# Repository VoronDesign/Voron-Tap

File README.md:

# Voron Tap

> Animated image courtesy of [Maple Leaf Makers](https://github.com/MapleLeafMakers) , see the whole video at https://www.youtube.com/watch?v=mz5qcOZgXhI

Tap is a nozzle-based z-probe for the V2 and Trident printer designs. The entire toolhead moves to trigger an optical switch. Tap offers many advantages:

* Extreme precision 0.4μm (0.0004mm)
* Any build surface and easily change at will
* Durability via optical sensor (millions of probe cycles)
* High temperature reliability (70C to 100C)
* Simplified probe mechanics (no dock/undock macros)
* No separate Z-endstop required
* Crash protection

## Requirements

* Bed must be stable for probing force of 500-800 grams
  * Switchwire, V1.8, Legacy, V0 beds are NOT rigid enough
* Mounts to MGN-12H X-axis
* Front mounted extruder (Clockwork2, LGX, Galileo)
* Accuracy depends on good mechanical condition
* Must have 5V at toolhead or special 24V sensor PCB

## Instructions

Comprehensive assembly details are available in the [Manual](Manual/Assembly_Manual_Tap.pdf)

## Post-Install Setup

1. Update your `printer.cfg` as recommended in [Tap Klipper Instructions](config/tap_klipper_instructions.md)
2. Test virtual Z endstop by lifting tool-head and using the `M119` or `query_probe` commands
3. Home Z.
4. Heat soak your machine and run a couple `probe_accuracy samples=100` to "break-in" your probe and check there's no significant trend in the result
5. Run a few more `probe_accuracy` checks (default of 10 probes)

### Diagnosing problems

For well-built machines you can expect to see between 0.0000 and 0.0008 standard deviation. Where probe accuracy trends notably up/down over 100 samples, or standard deviation is outside the desired range, check that:
- Sampling is taking place at a constant temperature (cooling/heating of any part will result in drift)
- Z belts are tightened correctly and uniformly
- The magnets on your tap have been adjusted to mate correctly when Tap is in the down position ([see the adjustment step in Nero3D's build guide](https://youtu.be/mJNCn72lQpU?t=751))
- The rail is well greased, the balls are correctly seated and there's no swarf in the guides (eg from the manufacture)
- The StealthBurner is firmly attached onto the Tap carriage
  - A common mistake is that the tabs on the body of the SB are pushed up under the alignment screws on the carriage to seat it in place, but then not tightened - make sure to tighten these firmly!
- The `speed` parameter in the `[probe]` section of your `printer.cfg` is appropriate (try `speed: 3` with `lift_speed: 10`)
- Several runs of `probe_accuracy samples=100` have been run (it can take a little while to bed in the rail)

While originally intended for the klicky probe, the following [probe accuracy tests](https://github.com/sporkus/probe_accuracy_tests) may assist in further diagnosis.

## FAQs

* Will Tap hurt my print surface? No, probing temp is restricted to 150C. The team recommends spray coated spring steel. Users of smooth PEI may find minor burnish marks if continously probing the same spot.
* Will the hartk 2-piece PCB work with Tap? Yes, but it requires a slight modification. See discord pin.
* Can I use an optical sensor not specified in the BOM? Not recommended, the team spent considerable time validating sensors in [BOM](BOM.md).
* Can I use micro-switch instead? Not recommended, but check here for more details: [Unklicky Tap](https://github.com/majarspeed/Unklicky/tree/main/Unklicky_TAP)
* Can I use Tap with kinematic bed mounts? Yes, if your bed is rigid up to 800 grams of force.
* Doesn't this add a lot of weight? The team explored many designs and landed on ~50 extra grams as good trade-off between rigidity and weight.
* Why do I need this if my induction probe works fine? Tap enables a far better user experience as it eliminates most baby-stepping needed due to thermal expansion, nozzle & bed surface changes.
* Is Tap noticably more accurate than klicky? Yes.

## (Bonus Points) Data Science

Tap engineering is backed by data science. If you want to dive deeper check out the following resources:

* [Voron:LIVE! Voron Tap announcement stream](https://www.youtube.com/watch?v=JLUDLJQXZeU)
* [Probe accuracy across thermal envelope](https://github.com/KiloQubit/probe_accuracy)
* [Repeatability at individual corners](https://github.com/sporkus/probe_accuracy_tests)

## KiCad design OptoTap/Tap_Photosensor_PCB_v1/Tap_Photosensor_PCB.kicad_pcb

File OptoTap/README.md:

# OptoTap PCB

OptoTap PCB is a small, completely unnecessary PCB that exists to make installation of the optical sensor marginally more convenient. (That's right, several of us have spent dozens of hours and hundreds of dollars in order to avoid two solder joints and a bit of heat shrink.)

It comes in two official flavors/form factors:

- **V1**: smaller form factor, 5V only
- **V2**: taller form factor, 5 or 24V capable

Both simplify optical sensor installation by including the necessary current-limiting resistor for the IR led within the sensor itself, as well as providing a visible LED indicator to assist with troubleshooting. 

The V1 board attempts to minimize size and cost as much as possible, at the expense of some flexibility: it **can not be used as a drop-in replacement for 24V inductive sensors** (24V will fry the optical sensor, eventually.)

The V2 board adds a switch-mode regulator to allow safely connecting to 24V probe headers. The regulator converts positive input voltage between >5V and 24V to 5V on-board, at the expense of some additional components and a larger PCB. **Please read important information about previous versions of this board below.**

## OptoTap V1

This version saves some vertical room by requiring you to solder your connector wires directly to the board.

**Do not connect this version to 24V!** (Did we mention that *it's not 24V tolerant???*) Many of the Voron toolhead PCBs in circulation send 24V to the three-pin probe header. You cannot plug this board directly in to these headers!

### Revision history 

- 1.0: initial release
- 1.3: updated release
	- hybrid footprint to permit use of EE-SX398 sensor in addition to Optek versions
	- two-color LED to indicate status and assist with troubleshooting.
	- 'Dark Mode' solder jumper to allow turning off indicator LEDs
	- increased thermal relief on solder pads to make through-holes easier to solder

## OptoTap V2

This version uses an AP63205WU switch mode regulator to drop input voltage and supply 5V to the sensor. This gives a bit of additional room to add a 3-pin JST-PH 2.0mm pitch connector as well [part number S3B-PH-K-S (LF)(SN)].

**IMPORTANT NOTE: The original version of this board had an issue that rendered it unsafe for use at 24V**. Please see [this issue](https://github.com/VoronDesign/Voron-Tap/issues/42#issuecomment-1370065351) for more extensive details on the testing and resolution of the problem. 

The current version (V2.4) fixes the inrush overvoltage spike that plagued the initial release, and adds several additional safeguards, including a polyfuse and a reverse polarity protection diode.

### Usage notes

#### Operation at 5V

The V2.4 OptoTap PCB has been tested to work fine from 5V to 24V inputs with no modifications. However, this does induce a bit of additional voltage drop from the switching regulator IC going into LDO mode. If you would like to run the V2.4 OptoTap at 5V, my first suggestion would be to just run it at 5V with no modifications. It will most likely work just fine. 

However, it does have the capacity to bypass the whole buck converter circuit. Note that this also bypasses the polyfuse, so there will be no overcurrent protection. 

To make this modification, you need to cut the trace between the center pad and 24V pad on the rear of the PCB, then use some solder to bridge the center pad to the 5V pad. To reverse the change, just desolder that bridge and re-connect the center pad to the 24V pad with more solder. 

### Revision history

- 2.0: initial prototype
- 2.1: component modifications after initial testing
  - changed C1 to higher voltage rating
  - changed C2 bootstrap cap to higher capacitance
  - changed all capacitors to 0805 for better part availability
- 2.4: updated release
  - added polyfuse to limit overcurrent and damp inrush current-induced voltage spike on hot-plugging
  - added reverse polarity protection diode 
  - increased size of inductor to prevent coil saturation
  - added a second output filter capacitor to reduce output voltage ripple
  - hybrid footprint to permit use of EE-SX398 sensor in addition to Optek versions
  - two-color LED to indicate status and assist with troubleshooting.
  - 'Dark Mode' solder jumper to allow turning off indicator LEDs
  - added 5V/24V selection solder jumper on rear of board to allow for easy bypassing of voltage regulator circuit
  - increased thermal relief on solder pads to make through-holes easier to solder

### Ordering and Assembly notes

#### Inductor choice

I've tested version of this PCB with inductors from Cenker 
CKCS3012-4.7uH/M (C354557) and Microgate 
MPIT3015-4R7M-LF (C486485). Any 30xx footprint coil inductor with >1A current rating and ~ 100 mΩ DCR should work ok.

#### Indicator LED placement

For some reason, JLCPCB has trouble with their part orientation for this LED specifically. I'm hoping that eventually they will sort their database out. In the meantime, it is worth verifying the part placement prior to assembly.

The footprint silkscreen has two elements to help indicate the orientation of the LED: an extra line on the side to indicate Pin 1, and a little arrow that matches up with a corresponding arrow on the part:

For the v2.4 PCB, make sure that the arrow on the DFM points to the arrow on the footprint, pin 1 matches the extra line on the footprint, and the + pad matches up to the correct pad! 

This is how it will look when assembled:

You can see the little bond wires from each of the three LEDs going back to the common anode, which is pretty neat.

***NOTE THAT THE 5V ONLY BOARD (V1.3) HAS A ROTATED FOOTPRINT! YOU'RE WELCOME AND I'M SORRY.***

## Indicator LEDs

The revised boards (V1.3/2.4) now have two-color indicator LEDs to help assist with troubleshooting. This should hopefully help a little bit with troubleshooting. The expected behavior of the LED is:

- Blue: Connected to power, beam not broken
- Red: Connected to power, beam broken

When installed in the toolhead, the light should be red normally (toolhead in 'down' position) and blue when activated (toolhead in 'up') position.

I would suggest powering on the board with 5V prior to installing it to make sure everything is functioning as expected. If the indicator LED is red with nothing blocking the optical sensor beam path, there is probably a problem with the ground and signal wires -- triple check!

## Sensor Choice

### Omron or Optek

The revised versions of the boards (V1.3 and V2.4) feature a hybrid optical sensor footprint that permits installation of the Omron EE-SX398 sensor in addition to the Optek OPB666/9xx versions. In testing, the Omron sensor performed just as well as the Optek sensor. 

However, it has a *slightly* different footprint than the Omron sensor, with annoyingly-close leads on the three pin side. I went through a few iterations of testing to come up with a hybrid footprint that seems to work well for either sensor model.

The slots mean there is a little play in sensor positioning, particularly with the EE-SX398 sensor. To help ensure precise alignment with this sensor, print out the jig included in the [STLs](./STLs) folder.

### Sensor Logic

The Tap setup requires a *buffer* style circuit rather than an *inverter* style to ensure safe operation. This style causes the sensor to trigger (pull the signal pin low) when the toolhead is in its normal, 'down' position. That means that if there is a bad connection somewhere, the MCU can observe that there is a problem *without* crashing the toolhead uncontrollably into the build plate.

Please double check your sensor part number to make sure you're getting the appropriate model!

#### For Omron:

- **Good**:
  - EE-SX398
- **Bad**: 
  - EE-SX498

#### For Optek:

- **Good**: 
  - OPB666N
  - OPB9x1
- **Bad**:
  - OPB9x2

Additionally, for the Optek probes, the OPB9x0 sensors are totem pole rather than open collector, meaning that they will pull the sense pin up to 5V when not pulling it down to GND. This can cause problems for some boards (notably RP2040-based CAN toolhead boards) that do not have 5V-tolerant endstop pins.

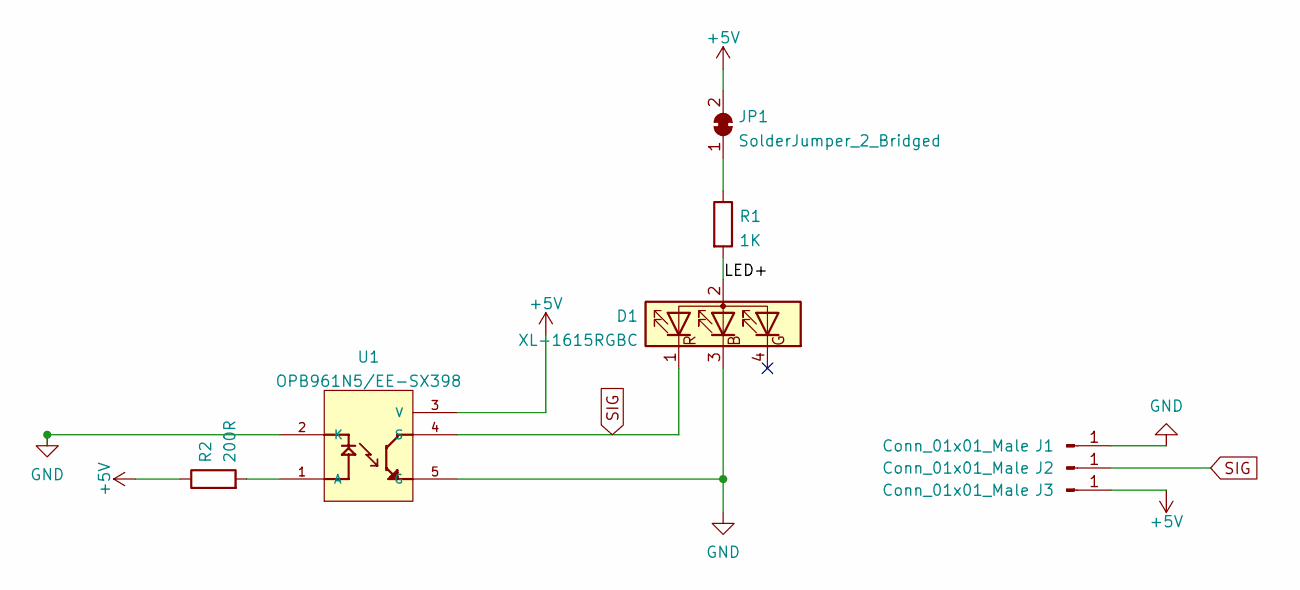
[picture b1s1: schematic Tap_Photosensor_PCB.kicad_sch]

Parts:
D1: XL-1615RGBC; LED_0606_1432; LCSC C965840
J1, J2, J3: Conn_01x01_Male; PinHeader_1x01_P2.54mm_Vertical
JP1: SolderJumper_2_Bridged; SolderJumper-2_P1.3mm_Bridged_RoundedPad1.0x1.5mm
R1: 1K; R_0805_2012Metric; LCSC C17513
R2: 200R; R_0805_2012Metric; LCSC C17540
U1: OPB961N5/EE-SX398; OPTO_EE-SX398_OPB666N; PARTREV NA

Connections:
+5V: J3.1, JP1.2 (B), R2.1, U1.3 (V)
/LED+: D1.2 (A), R1.2
GND: D1.3 (B), J1.1, U1.2 (K), U1.5 (G)
unnamed: JP1.1 (A), R1.1
unnamed: R2.2, U1.1 (A)
SIG: D1.1 (R), J2.1, U1.4 (S)

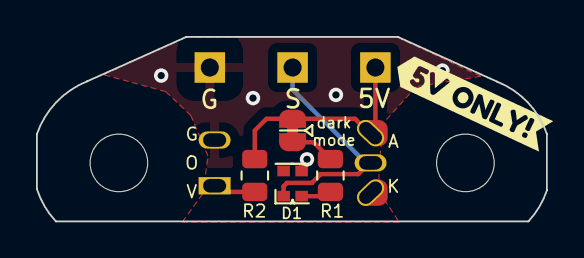
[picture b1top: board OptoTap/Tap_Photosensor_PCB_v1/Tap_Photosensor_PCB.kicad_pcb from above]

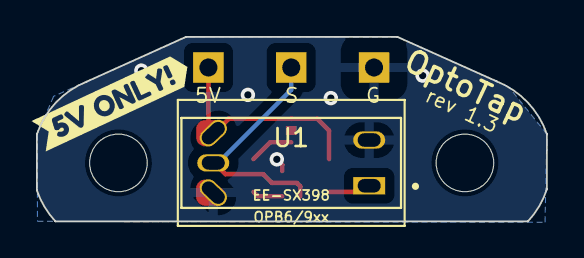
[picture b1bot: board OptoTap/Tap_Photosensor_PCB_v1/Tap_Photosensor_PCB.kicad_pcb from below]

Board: 2 copper layers, 28.3 x 10.2 mm, 10 parts (2 on the bottom side), 6 nets.

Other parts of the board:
kibuzzard-6366BF75: G***; kibuzzard-6366BF75
kibuzzard-6366C103: G***; kibuzzard-6366C103

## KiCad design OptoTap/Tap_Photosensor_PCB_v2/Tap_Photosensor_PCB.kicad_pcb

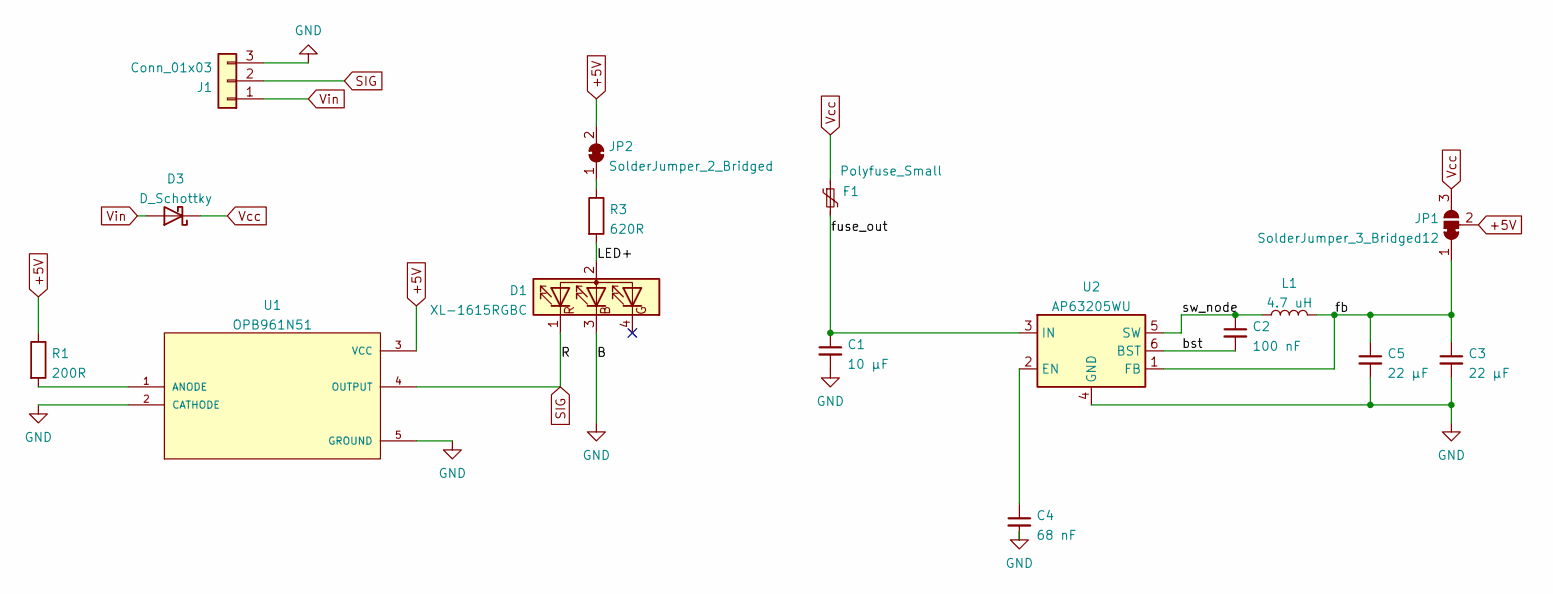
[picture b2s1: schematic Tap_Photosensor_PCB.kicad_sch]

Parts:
C1: 10 µF; C_0805_2012Metric; PARTNUM GRM21BR61H106KE43L; LCSC C440198
C2: 100 nF; C_0402_1005Metric; PARTNUM CL05B104KB54PNC; LCSC C307331
C3, C5: 22 µF; C_0603_1608Metric; PARTNUM GRM188R61A226ME15D; LCSC C84419
C4: 68 nF; C_0402_1005Metric; PARTNUM CC0402KRX7R9BB683; LCSC C354977
D1: XL-1615RGBC; LED_0606_1432; LCSC C965840
D3: D_Schottky; D_SOD-323; PARTNUM CUS10S30,H3F; LCSC C146335
F1: Polyfuse_Small; R_0805_2012Metric; PARTNUM SMD0805-010-33V; LCSC C2840557
J1: Conn_01x03; JST_PH_S3B-PH-K_1x03_P2.00mm_Horizontal
JP1: SolderJumper_3_Bridged12; SolderJumper-3_P1.3mm_Bridged12_RoundedPad1.0x1.5mm_NumberL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
JP2: SolderJumper_2_Bridged; SolderJumper-2_DARKMODE
L1: 4.7 uH; CKCS3010; PARTNUM CKCS3012-4.7uH/M; LCSC C354557
R1: 200R; R_0603_1608Metric; PARTNUM 0603WAF2000T5E; LCSC C8218
R3: 620R; R_0603_1608Metric; PARTNUM 0603WAF6200T5E; LCSC C23220
U1: OPB961N51; OPTO_EE-SX398_OPB666N; PARTREV D
U2: AP63205WU; TSOT-26; PARTNUM AP63205WU; LCSC C2071056

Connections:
+5V: JP1.2 (C), JP2.2 (B), R1.1, U1.3 (VCC)
/LED+: D1.2 (A), R3.2
/bst: C2.2, U2.6 (BST)
/fb: C3.1, C5.1, JP1.1 (A), L1.2, U2.1 (FB)
/fuse_out: C1.1, F1.2, U2.3 (IN)
/sw_node: C2.1, L1.1, U2.5 (SW)
GND: C1.2, C3.2, C4.2, C5.2, D1.3 (B), J1.3, U1.2 (CATHODE), U1.5 (GROUND), U2.4 (GND)
unnamed: JP2.1 (A), R3.1
unnamed: R1.2, U1.1 (ANODE)
unnamed: C4.1, U2.2 (EN)
SIG: D1.1 (R), J1.2, U1.4 (OUTPUT)
Vcc: D3.1 (K), F1.1, JP1.3 (B)
Vin: D3.2 (A), J1.1

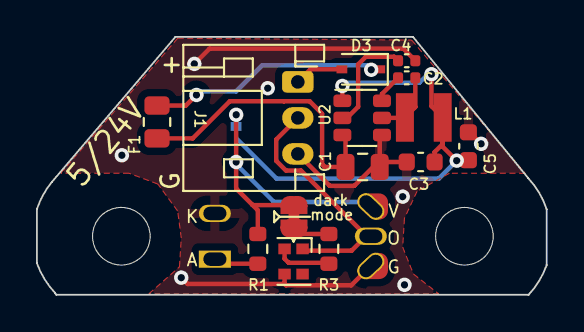
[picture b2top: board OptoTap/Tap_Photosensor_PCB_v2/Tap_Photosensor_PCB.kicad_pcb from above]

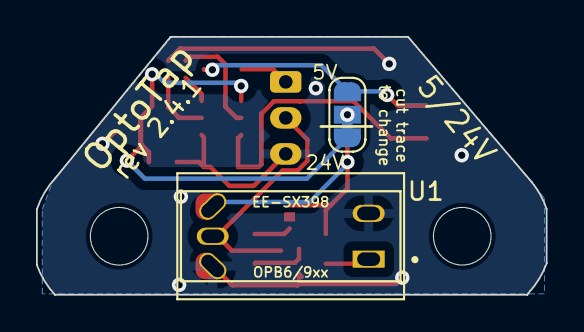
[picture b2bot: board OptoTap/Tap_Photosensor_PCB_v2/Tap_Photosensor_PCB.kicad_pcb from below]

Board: 2 copper layers, 28.3 x 14.3 mm, 16 parts (2 on the bottom side), 13 nets.

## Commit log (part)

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2022-11-22 Create TAP_BOM
2022-11-23 Add bom (#1)
    * Create TAP_BOM
    * Delete TAP_BOM
    * Create TAP_BOM.txt
    * Delete TAP_BOM.txt
    * Create TAP_BOM.md
    * Update TAP_BOM.md
2022-11-23 readme.md
2022-11-23 initial commit of stls
2022-11-23 CAD upload
2022-11-24 Delete readme.md
    No need for a readme here
2022-11-25 Creating OptoTap space
2022-11-26 adding tap_klipper_instructions.md
2022-11-26 Delete tap_klipper_instructions.md
    added wrong file...
2022-11-26 readding tap_klipper_instructions
2022-11-26 Delete Readme.md
    not needed
2022-11-26 Create readme.md
    adding manual dir
2022-11-26 Manual commit!
2022-11-26 Delete Tap_Magnet_left_r1.stl
    removing to rename
2022-11-26 Delete TAP_Upper_Wired_r1.stl
    removing to rename
2022-11-26 Delete TAP_Upper_PCB_r1.stl
    removing to rename
2022-11-26 renamed files
2022-11-26 Delete readme.md
    reorganizing
2022-11-26 Delete README.md
    replacing
2022-11-26 Update README.md
    x carriage->X carriage
2022-11-26 Delete Assembly_Manual_TAP.pdf
    updating capitalization and filenames
2022-11-26 Add files via upload
    reconciled filename capitalization and versioning
2022-11-26 Delete deleteme.md
    removing unused file
2022-11-26 updating per KiloQubit
    in klipper instructions, remove <!-- {% raw %} --> and <!-- {% endraw %} -->, they should just be empty lines there, it's not jinja
2022-11-27 updating CAD name
    lowercase
2022-11-27 renaming to Tap
2022-11-27 add gitignore
2022-11-27 add gitignore (#3)
2022-11-27 Initial commit of the STLs and CAD for Voron-Tap (#2)
    * Create Readme.md
    * readme.md
    * Create readme.md
    * initial commit of stls
    * CAD upload
    * Delete readme.md
2022-11-27 removed zip archive
2022-11-27 added optotap files
2022-11-27 Optotap (#4)
    * removed zip archive
    * added optotap files
2022-11-27 Add missing tool STLs (#5)
2022-11-27 temp to hold directory open
2022-11-27 removing old
2022-11-27 updated optotap link
2022-11-27 removing temp file
2022-11-27 updating the optotap link in manual (#6)
    * temp to hold directory open
    * removing old
    * updated optotap link
    * removing temp file
2022-11-27 Update .gitignore (#8)
    * Update .gitignore
    * Update .gitignore
2022-11-27 fixed PCB assembly files
2022-11-27 fixed PCB assembly files (#9)
2022-11-27 updated kicad files with proper resistor values
2022-11-27 updated kicad files with proper resistor values (#11)
2022-11-28 fixed merge conflict
2022-11-28 Fix a bad merge, fixing the BOMs
2022-11-28 fixed merge conflict (#12)
2022-11-28 Create temp
2022-11-28 Add files via upload
    fixed issues with pixelated drawings and truncated texts
2022-11-28 fixing a few more issues noticed
2022-11-28 fixing images in manual, also minor text truncations (#16)
    * temp to hold directory open
    * removing old
    * updated optotap link
    * removing temp file
    * Create temp
    * Delete Assembly_Manual_Tap.pdf
2022-11-29 Addressing #15
    https://github.com/VoronDesign/Voron-Tap/issues/15 I reduced the chamfer. while in there I also update the part to voron-red
2022-11-29 reduced chamfer for more mgn12 clearance
2022-11-29 Delete [a]Tap_Center_r1.stl
    removing older version with too much chamfer https://github.com/VoronDesign/Voron-Tap/issues/15
2022-11-29 updating cad for issue 15
2022-11-29 Reducing chamfer on Tap_center per issue #15 (#17)
    * temp to hold directory open
    * removing old
    * updated optotap link
    * removing temp file
    * Create temp
    * Delete Assembly_Manual_Tap.pdf
2022-11-29 putting back the support which went missing in r2
2022-11-29 Delete [a]Tap_Center_r2.stl
    removing the support-less version
2022-11-29 Create changelog.md
    Adding a changelog for summarizing part changes
2022-11-29 correcting part names, adding link
2022-11-29 re-added missing center support from r2
2022-11-29 Delete VORON_Tap_r2.step
    removing older cad
2022-11-29 fixed missing support in [a]Tap_Center_r2 (#18)
    * putting back the support which went missing in r2
    * Delete [a]Tap_Center_r2.stl
    removing the support-less version
    * Create changelog.md
    Adding a changelog for summarizing part changes
    * correcting part names, adding link
2022-12-07 Update Readme.md with more info
2022-12-07 Spelling fixes based on feedback
    Additional FAQs
2022-12-07 Add another FAQ
    Regarding surface exposure
2022-12-07 Include gif in repo
2022-12-08 Feedback tweaks from @tanaes
2022-12-08 Update Readme.md with more info (#22)
    * Update Readme.md with more info
    * Spelling fixes based on feedback
    Additional FAQs
    * Add another FAQ
    Regarding surface exposure
    * Include gif in repo
2022-12-14 updated README with part number
2022-12-14 updated README with part number (#29)
2022-12-15 Add image citation.
2022-12-15 terminology update
2022-12-15 Add image citation. (#30)
    * Add image citation.
    * terminology update
2022-12-17 Mid-December tap update
    Added D2HW variant
    minor adjustments to wired and PCB optical sensor position
    minor clearance adj to m3x12 endstop
    clearance for solder blobs
2022-12-17 remove prev cad version
2022-12-17 tightened up optical channel by .6mm
2022-12-17 mid december update
    D2HW variant introduced
    minor changes to optical sensor positions to improve precision
    added reinforcement to center above magnet holders
2022-12-17 removing older version
2022-12-17 Delete Tap_Upper_PCB_r1.stl
    removing older version
2022-12-17 Delete Tap_Upper_Wired_r1.stl
    removing older version
2022-12-17 Delete [a]Tap_Center_r3.stl
    removing older version
2022-12-17 Update changelog.md
    Mid december update
2022-12-17 mid december update
    Addressing:
    https://github.com/VoronDesign/Voron-Tap/issues/25
    https://github.com/VoronDesign/Voron-Tap/issues/24
    https://github.com/VoronDesign/Voron-Tap/issues/23
    https://github.com/VoronDesign/Voron-Tap/issues/20
    https://github.com/VoronDesign/Voron-Tap/issues/19
2022-12-17 mid december update
2022-12-17 adding pictorial changelog
2022-12-17 fixing link
2022-12-17 fixing minor issues in visual changelog
2022-12-17 Delete Assembly_Manual_TAP.pdf
    wrong file name
2022-12-17 manual updated
    https://github.com/VoronDesign/Voron-Tap/issues/25
    https://github.com/VoronDesign/Voron-Tap/issues/24
    https://github.com/VoronDesign/Voron-Tap/issues/23
    https://github.com/VoronDesign/Voron-Tap/issues/20
    https://github.com/VoronDesign/Voron-Tap/issues/19
    https://github.com/VoronDesign/Voron-Tap/issues/14
2022-12-17 Update tap_klipper_instructions.md
    - closes issue #27
    - adds reminder to remove old autosaved `position_endstop` value for `stepper_z` if present
    - improves readability
2022-12-17 Mid december update (#32)
    * Mid-December tap update
    Added D2HW variant
    minor adjustments to wired and PCB optical sensor position
    minor clearance adj to m3x12 endstop
    clearance for solder blobs
    * remove prev cad version
2022-12-17 Update tap_klipper_instructions.md (#33)
    - closes issue #27
    - adds reminder to remove old autosaved `position_endstop` value for `stepper_z` if present
    - improves readability
2022-12-19 Update tap_klipper_instructions.md
    Update QGL locations as nozzle is probe location.
2022-12-19 Update tap_klipper_instructions.md
    Update to formatting
2022-12-27 Add "Z" ("w/ wires") to the PN (OPB991L11Z).
2023-01-02 Add "Z" ("w/ wires") to the PN (OPB991L11Z). (#39)
2023-01-03 Add files via upload
    Improved Belt routing:
    1)teeth moved 0.6mm so that they do not cause binding issues by stressing out the endcaps of the MGN12H
    2)belt management details improved (on the "front" side of Tap_center) fro added strength and lower profile.
2023-01-03 Add files via upload
    r5 tap_center reduces binding caused by belt stress on MGN12H.
    also reduces bending of part.
    improves belt management
2023-01-03 Delete [a]Tap_Center_r4.stl
    removing old tap_center
2023-01-03 logupdate
2023-01-03 for changelog
2023-01-03 Fix for X-Axis binding (#43)
    * Mid-December tap update
    Added D2HW variant
    minor adjustments to wired and PCB optical sensor position
    minor clearance adj to m3x12 endstop
    clearance for solder blobs
    * remove prev cad version
2023-01-04 Add files via upload
    fixing a minor ledge artifact in tap_center.
2023-01-04 fixed a minor ledge artifact
2023-01-04 Delete 1_3_23updatelog.png
    updating
2023-01-04 Add files via upload
    updated to include 2 more changes
2023-01-04 Update to the jan 3 update (#44)
    * Add files via upload
    fixing a minor ledge artifact in tap_center.
    * fixed a minor ledge artifact
    * Delete 1_3_23updatelog.png
    updating
    * Add files via upload
2023-01-13 update magnet holders from CAD
2023-01-14 update magnet holders from CAD (#46)
2023-03-02 updated OptoTap boards
2023-03-03 changed footprint text to specify EE-SX398
2023-03-03 added solder jig step
2023-03-03 fixed link
2023-03-03 updated OptoTap boards (#53)
    * updated OptoTap boards
    * changed footprint text to specify EE-SX398
    * added solder jig step
    * fixed link
2023-03-25 add quad_gantry_level points to instructions
2023-05-01 Updating to RC8
2023-05-01 renaming step to VORON_Tap_RC8
2023-05-01 r8 stl files uploaded
2023-05-01 adding in readme
2023-05-01 Create placeholder
2023-05-01 adding images for r8 readme
2023-05-01 Updating to RC8
    badnoob: rename step to VORON_Tap_RC8
    badnoob: r8 stl files uploaded
    badnoob: add R8 readme
    jade: move rc8 images, update readme image paths
2023-05-01 Standardize file names, remove old revisions
2023-05-01 Updating to RC8 (#62)
    * Updating to RC8
    badnoob: rename step to VORON_Tap_RC8
    badnoob: r8 stl files uploaded
    badnoob: add R8 readme
    jade: move rc8 images, update readme image paths
    * Standardize file names, remove old revisions
2023-05-06 Updated BOM.md to RC8
2023-05-06 Updated BOM.md to RC8 (#64)
2023-05-07 Renamed to denote accent part
    Keeping in line with prior releases and standard Voron printed part naming conventions, I've renamed "Tap_Center_r8.stl" to "[a]_Tap_Center_r8.stl"
2023-05-07 Renamed "Tap_Belt_Cover_r8_x2.stl" to "[a]_Tap_Belt_Cover_r8_x2.stl"
    Keeping in line with Voron printed part naming conventions, "Tap_Belt_Cover_r8_x2.stl" has been renamed to "[a]_Tap_Belt_Cover_r8_x2.stl"
2023-05-08 Renamed "Tap_Center_r8.stl" to "[a]_Tap_Center_r8.stl" and "Tap_Belt_Cover_r8_x2.stl" to "[a]_Tap_Belt_Cover_r8_x2.stl" (#66)
    * Renamed to denote accent part
    Keeping in line with prior releases and standard Voron printed part naming conventions, I've renamed "Tap_Center_r8.stl" to "[a]_Tap_Center_r8.stl"
    * Renamed "Tap_Belt_Cover_r8_x2.stl" to "[a]_Tap_Belt_Cover_r8_x2.stl"
    Keeping in line with Voron printed part naming conventions, "Tap_Belt_Cover_r8_x2.stl" has been renamed to "[a]_Tap_Belt_Cover_r8_x2.stl"
2023-05-16 Rename some R8 STL files to match the R1 manual
2023-05-17 updated STEP and kicad
2023-05-17 updated inductor info
2023-05-17 updated README with LED ordering info
2023-05-17 fixed bad save
2023-05-17 Opto24 (#68)
    * updated OptoTap boards
    * updated inductor info
    * updated STEP and kicad
    * updated README with LED ordering info
    * fixed bad save
2023-05-18 doc: add nr of pins for JST-PH connector
2023-06-13 ci: update dependencies
2023-06-13 ci: update task name
2023-06-14 address review comment
    revert name
2023-06-14 ci: update dependencies (#74)
    * ci: update dependencies
    * ci: update task name
    * address review comment
    revert name
2023-06-14 doc: add nr of pins for JST-PH connector (#69)
2023-07-27 clarified info on 5v operation
2023-08-18 clarified info on 5v operation (#77)
2023-09-20 Update CI node to 16.
2023-09-20 Update CI node to 16. (#80)
2024-01-17 DOC: Added diagnosis section to README and improved order of post-install checks
2024-01-19 Improve diagnostics section with additional checks
2024-01-19 DOC: Fixed syntax in example probe speed note
2024-01-19 DOC: Additional advice on bedding in
2025-06-07 add chinese readme
